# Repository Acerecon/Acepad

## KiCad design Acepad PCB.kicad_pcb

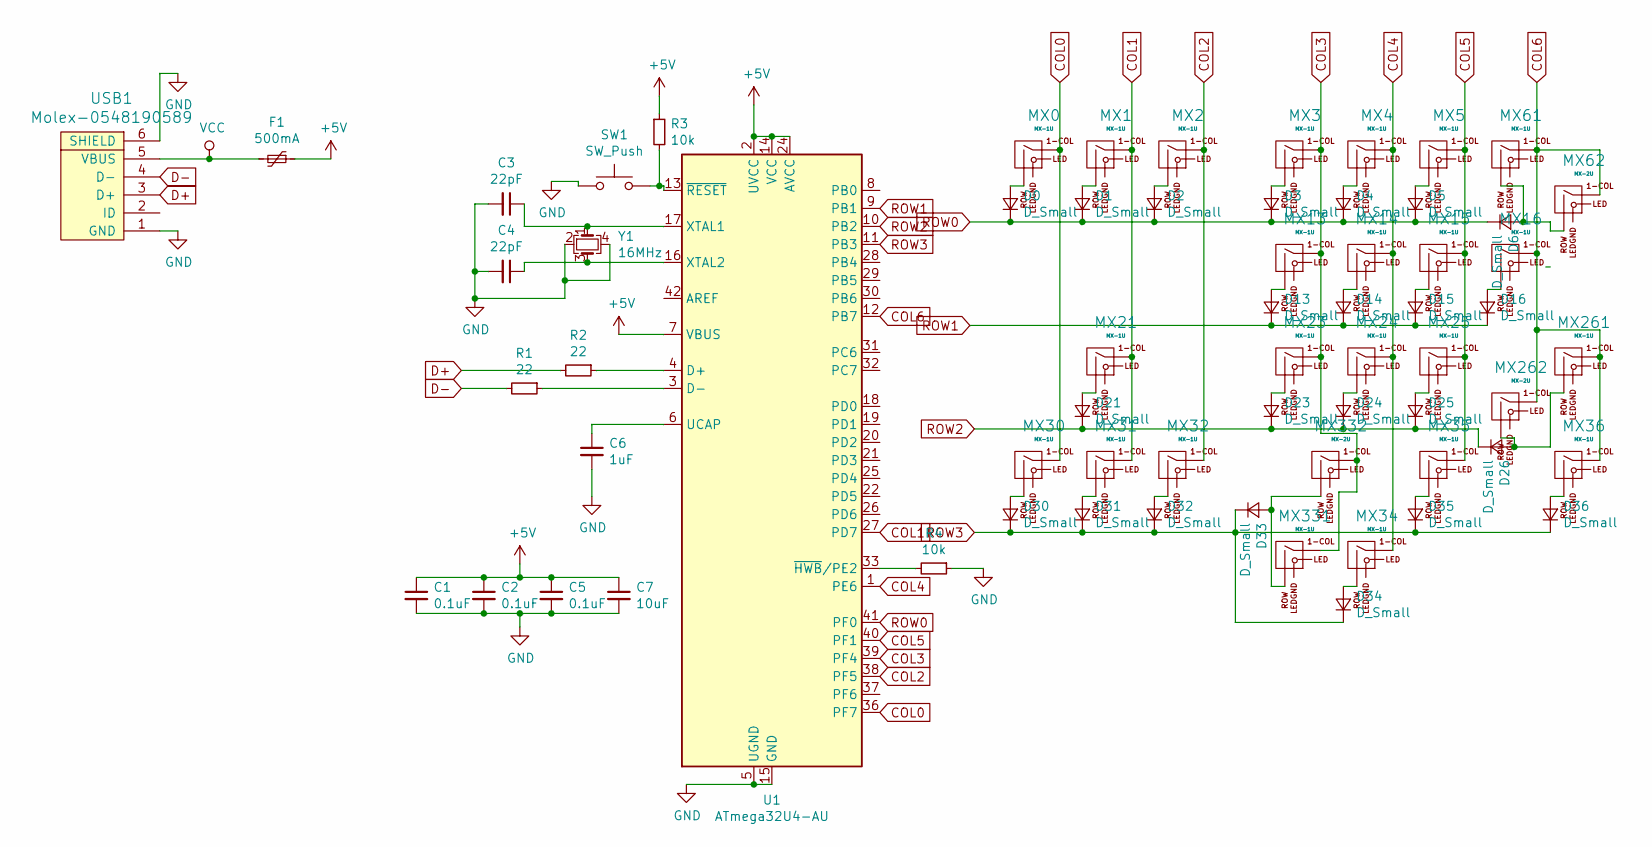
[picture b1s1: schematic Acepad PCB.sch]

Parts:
C1, C2, C5: 0.1uF; C_0805_2012Metric
C3, C4: 22pF; C_0805_2012Metric
C6: 1uF; C_0805_2012Metric
C7: 10uF; C_0805_2012Metric
D0, D1, D2, D3, D4, D5, D6, D13, D14, D15, D16, D21, D23, D24, D25, D26, D30, D31, D32, D33, D34, D35, D36: D_Small; D_SOD-123
F1: 500mA; Fuse_SMD1206_Reflow
MX0, MX1, MX2, MX3, MX4, MX5, MX13, MX14, MX15, MX16, MX21, MX23, MX24, MX25, MX30, MX31, MX32, MX34, MX35, MX36, MX61, MX261, MX331: MX-1U
MX62, MX262, MX332: MX-2U; MX-2U-ReversedStabilizers
R1, R2: 22; R_0805_2012Metric
R3, R4: 10k; R_0805_2012Metric
SW1: SW_Push; SKQG-1155865
U1: ATmega32U4-AU; TQFP-44_10x10mm_P0.8mm
USB1: Molex-0548190589
Y1: 16MHz; Crystal_SMD_3225-4Pin_3.2x2.5mm

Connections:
+5V: C1.1, C2.1, C5.1, C7.1, F1.1, R3.1, U1.2 (UVCC), U1.7 (VBUS), U1.14 (VCC), U1.24 (AVCC), U1.34 (VCC), U1.44 (AVCC)
COL0: MX0.1 (COL), MX30.1 (COL), U1.36 (PF7)
COL1: MX1.1 (COL), MX21.1 (COL), MX31.1 (COL), U1.27 (PD7)
COL2: MX2.1 (COL), MX32.1 (COL), U1.38 (PF5)
COL3: MX3.1 (COL), MX13.1 (COL), MX23.1 (COL), MX331.1 (COL), MX332.1 (COL), U1.39 (PF4)
COL4: MX4.1 (COL), MX14.1 (COL), MX24.1 (COL), MX34.1 (COL), U1.1 (PE6)
COL5: MX5.1 (COL), MX15.1 (COL), MX25.1 (COL), MX35.1 (COL), U1.40 (PF1)
COL6: MX16.1 (COL), MX36.1 (COL), MX61.1 (COL), MX62.1 (COL), MX261.1 (COL), MX262.1 (COL), U1.12 (PB7)
D+: R2.2, USB1.3 (D+)
D-: R1.2, USB1.4 (D-)
GND: C1.2, C2.2, C3.2, C4.2, C5.2, C6.2, C7.2, R4.1, SW1.1, U1.5 (UGND), U1.15 (GND), U1.23 (GND), U1.35 (GND), U1.43 (GND), USB1.1 (GND), USB1.6 (SHIELD), Y1.2, Y1.4
unnamed: C3.1, U1.17 (XTAL1), Y1.1
unnamed: C4.1, U1.16 (XTAL2), Y1.3
unnamed: C6.1, U1.6 (UCAP)
unnamed: D0.2 (A), MX0.2 (ROW)
unnamed: D1.2 (A), MX1.2 (ROW)
unnamed: D2.2 (A), MX2.2 (ROW)
unnamed: D3.2 (A), MX3.2 (ROW)
unnamed: D4.2 (A), MX4.2 (ROW)
unnamed: D5.2 (A), MX5.2 (ROW)
unnamed: D6.2 (A), MX61.2 (ROW), MX62.2 (ROW)
unnamed: D13.2 (A), MX13.2 (ROW)
unnamed: D14.2 (A), MX14.2 (ROW)
unnamed: D15.2 (A), MX15.2 (ROW)
unnamed: D16.2 (A), MX16.2 (ROW)
unnamed: D21.2 (A), MX21.2 (ROW)
unnamed: D23.2 (A), MX23.2 (ROW)
unnamed: D24.2 (A), MX24.2 (ROW)
unnamed: D25.2 (A), MX25.2 (ROW)
unnamed: D26.2 (A), MX261.2 (ROW), MX262.2 (ROW)
unnamed: D30.2 (A), MX30.2 (ROW)
unnamed: D31.2 (A), MX31.2 (ROW)
unnamed: D32.2 (A), MX32.2 (ROW)
unnamed: D33.2 (A), MX331.2 (ROW), MX332.2 (ROW)
unnamed: D34.2 (A), MX34.2 (ROW)
unnamed: D35.2 (A), MX35.2 (ROW)
unnamed: D36.2 (A), MX36.2 (ROW)
unnamed: R1.1, U1.3 (D-)
unnamed: R2.1, U1.4 (D+)
unnamed: R3.2, SW1.2, U1.13 (~RESET)
unnamed: R4.2, U1.33 (~HWB~/PE2)
ROW0: D0.1 (K), D1.1 (K), D2.1 (K), D3.1 (K), D4.1 (K), D5.1 (K), D6.1 (K), U1.41 (PF0)
ROW1: D13.1 (K), D14.1 (K), D15.1 (K), D16.1 (K), U1.9 (PB1)
ROW2: D21.1 (K), D23.1 (K), D24.1 (K), D25.1 (K), D26.1 (K), U1.10 (PB2)
ROW3: D30.1 (K), D31.1 (K), D32.1 (K), D33.1 (K), D34.1 (K), D35.1 (K), D36.1 (K), U1.11 (PB3)
VCC: F1.2, USB1.5 (VBUS)

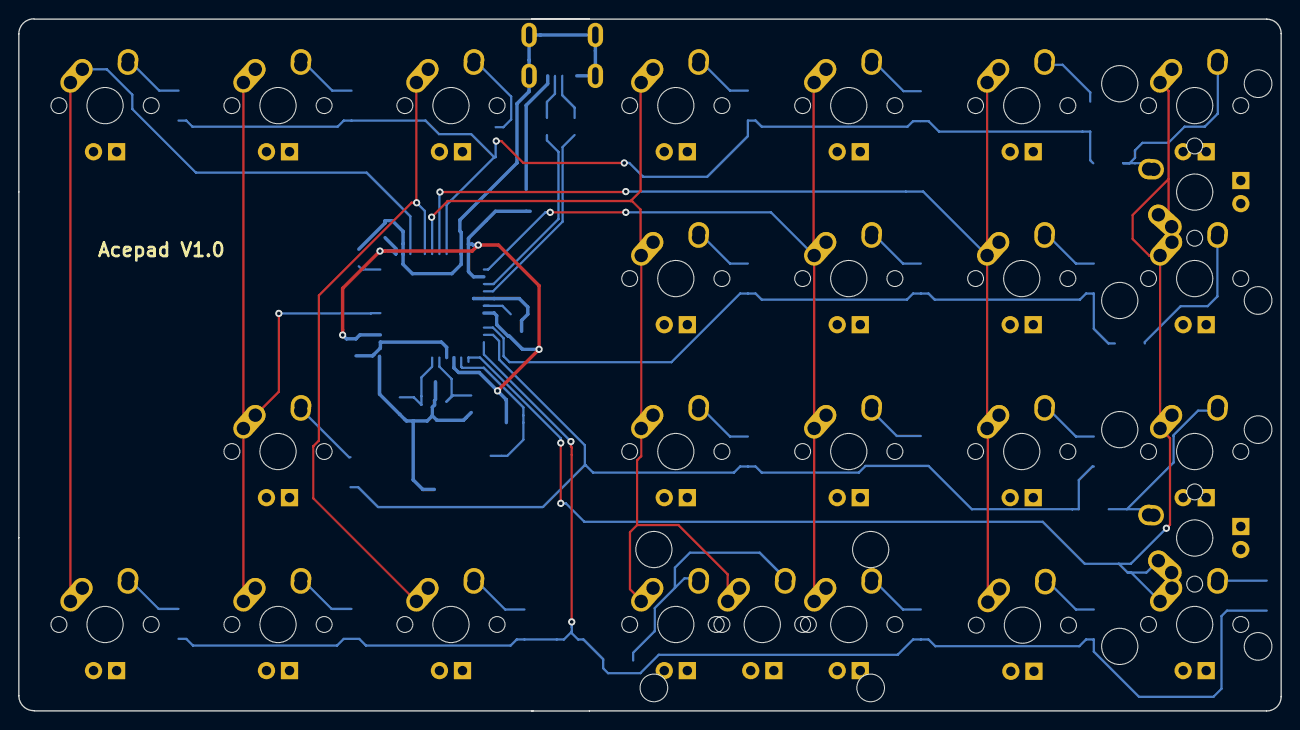
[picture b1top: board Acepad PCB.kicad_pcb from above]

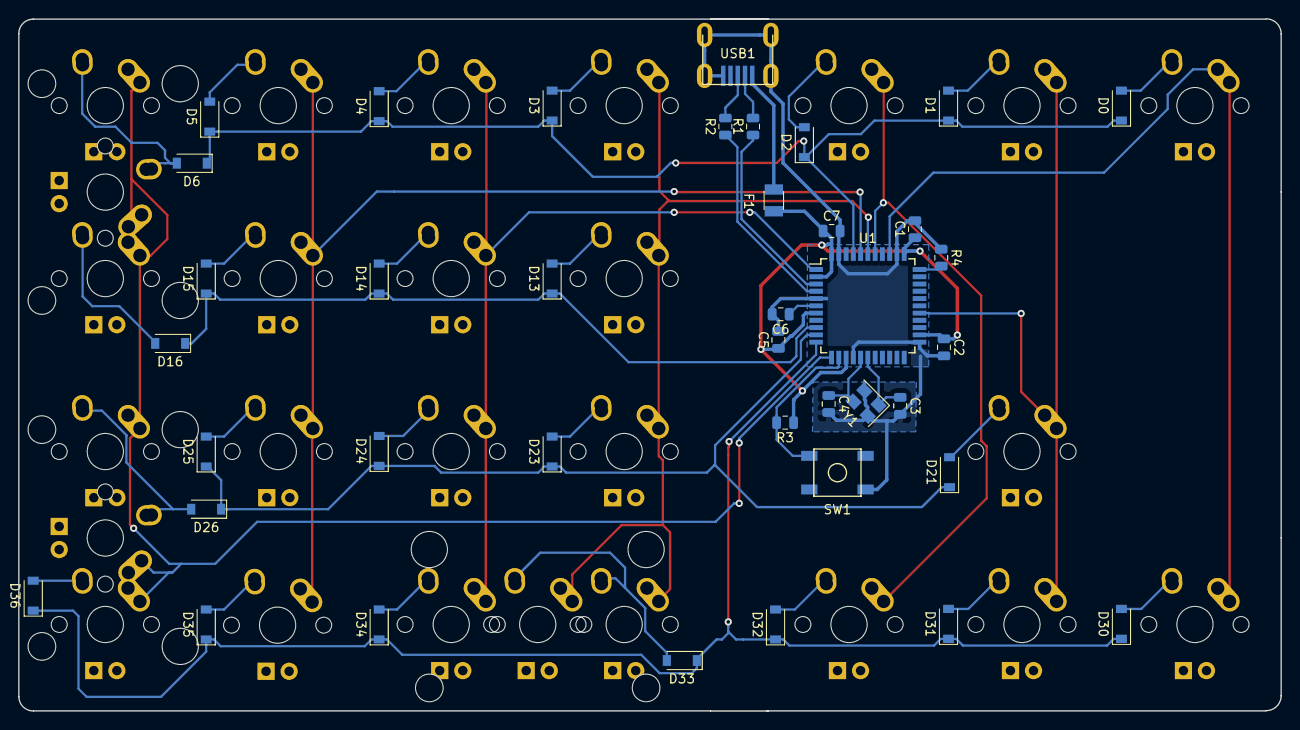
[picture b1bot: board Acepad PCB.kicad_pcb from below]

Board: 2 copper layers, 139.0 x 76.2 mm, 65 parts (39 on the bottom side), 46 nets.

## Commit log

2019-03-10 Added PCB files
2019-03-10 Add submodules
2019-03-10 Added libraries (no fp tryin figure out why)
2019-03-10 Added FP, updated PCB
2019-03-10 Generated netlist and continued work on PCB
2019-03-11 worked more on PCB
2019-03-12 worked on pcb
2019-03-13 continued work on pcb (flipped stabs, worked on wiring)
2019-03-14 continued working on pcb
